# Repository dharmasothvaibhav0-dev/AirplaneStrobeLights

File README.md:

# AirplaneStrobeLights

### This project is designed to replicate the strobe lights seen on flights. The lights flash on the sides of the wings and the top and back of the plane for better visibility.
I got inspiration for this when I went to the airport and saw the planes with these flashing lights, and I wanted to replicate it. 

## Schematic-

## PCB-

## Assembly- 

Its important that you place the LEDS as 2 on the sides, 1 in the middle, and 3 in the back as it is how it is in real life.
I made it so every component can be placed on the top of the PCB, I tried to design it to where it still had a decent look once all components were placed. 

As soon as you connect the plane to a USB A port(5v), it should automatically turn on and the leds will start to flash very quick.

## Components-

This is made up of 10 resistors, **Its very important to know that resistor #1 is 8.2k, and resistor #2 is 1k** All the rest are 220, be very careful. Also **Capacitor 1 is .01u, and Capacitor 2 is 10u**. When placing said resistors and capacitors capacitor 2 goes on the left of the NE555, and Capacitor 1 goes to the right. Resistor 1 goes to the top of capcitor 2, and resistor 2 goes to the top of capacitor 1. its VERY important you place them in the correct spots as seen below.

## Bill of Materials (BOM)

| Id                               | Footprint                                         | Quantity | Value   |
|----------------------------------|---------------------------------------------------|----------|---------|
| C1                               | C_Disc_D8.0mm_W5.0mm_P5.00mm                      | 1        | 0.01uF  |
| C2                               | C_Disc_D8.0mm_W5.0mm_P5.00mm                      | 1        | 10uF    |
| D1, D2, D3, D4, D5, D6, D7, D8   | LED_D5.0mm                                        | 8        | LED     |
| J1                               | USB_A_Molex_67643_Horizontal                      | 1        | USB_A   |
| R1                               | R_Axial_DIN0204_L3.6mm_D1.6mm_P7.62mm_Horizontal  | 1        | 8.2kΩ   |
| R2                               | R_Axial_DIN0204_L3.6mm_D1.6mm_P7.62mm_Horizontal  | 1        | 1kΩ     |
| R4, R5, R6, R7, R8, R9, R10, R11 | R_Axial_DIN0204_L3.6mm_D1.6mm_P7.62mm_Horizontal  | 8        | 220Ω    |
| U1                               | DIP-8_W7.62mm                                     | 1        | NE555P  |
| U2                               | DIP-16_W7.62mm                                    | 1        | CD4017  |

# I hope you enjoy building this! - Vaibhav :D

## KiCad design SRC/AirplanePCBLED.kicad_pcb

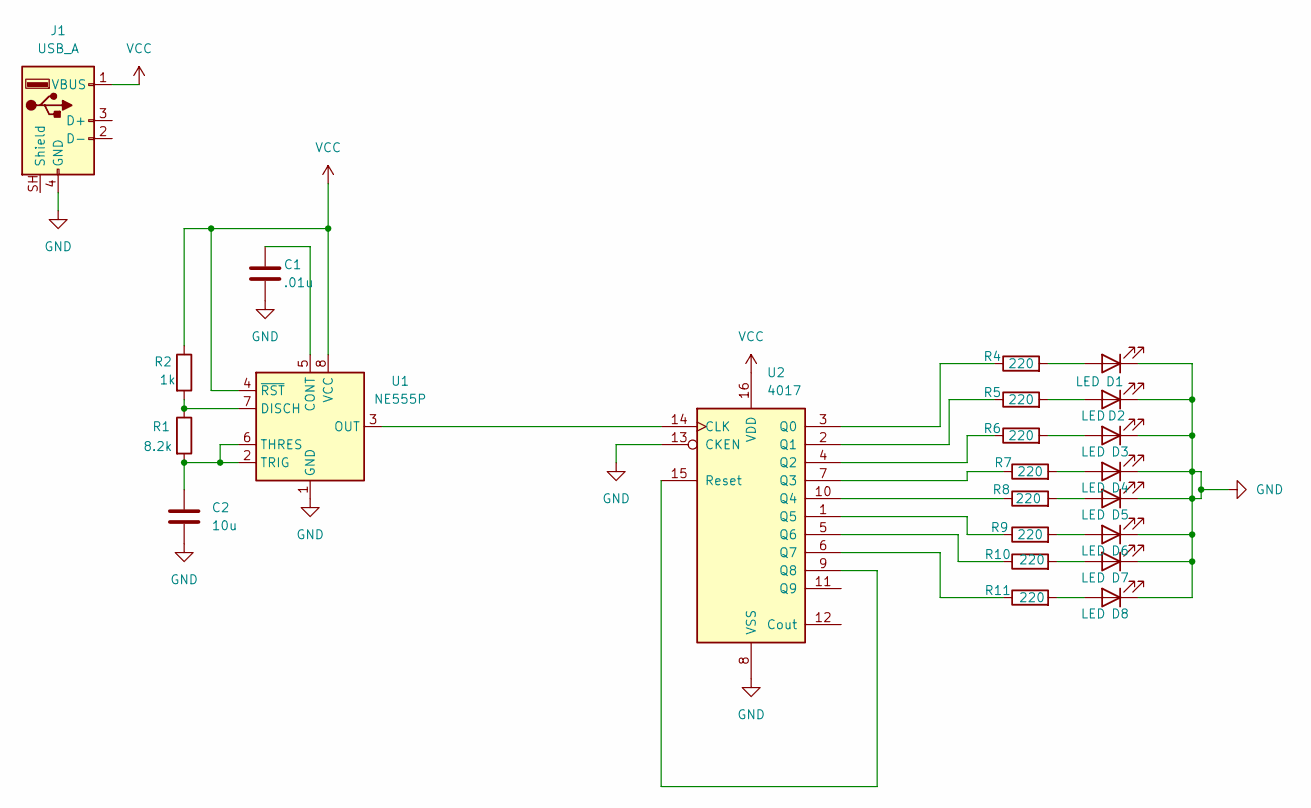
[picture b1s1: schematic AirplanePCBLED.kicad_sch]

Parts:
C1: .01u; C_Disc_D8.0mm_W5.0mm_P5.00mm
C2: 10u; C_Disc_D8.0mm_W5.0mm_P5.00mm
D1, D2, D3, D4, D5, D6, D7, D8: LED; LED_D5.0mm
J1: USB_A; USB_A_Molex_67643_Horizontal
R1: 8.2k; R_Axial_DIN0204_L3.6mm_D1.6mm_P7.62mm_Horizontal
R2: 1k; R_Axial_DIN0204_L3.6mm_D1.6mm_P7.62mm_Horizontal
R4, R5, R6, R7, R8, R9, R10, R11: 220; R_Axial_DIN0204_L3.6mm_D1.6mm_P7.62mm_Horizontal
U1: NE555P; DIP-8_W7.62mm
U2: 4017; DIP-16_W7.62mm

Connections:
GND: C1.2, C2.2, D1.1 (K), D2.1 (K), D3.1 (K), D4.1 (K), D5.1 (K), D6.1 (K), D7.1 (K), D8.1 (K), J1.4 (GND), U1.1 (GND), U2.8 (VSS), U2.13 (CKEN)
unnamed: D1.2 (A), R4.2
unnamed: D2.2 (A), R5.2
unnamed: D3.2 (A), R6.2
unnamed: D4.2 (A), R7.2
unnamed: D5.2 (A), R8.2
unnamed: D6.2 (A), R9.2
unnamed: D7.2 (A), R10.2
unnamed: D8.2 (A), R11.2
unnamed: C1.1, U1.5 (CONT)
unnamed: R1.1, R2.2, U1.7 (DISCH)
unnamed: U1.3 (OUT), U2.14 (CLK)
unnamed: C2.1, R1.2, U1.2 (TRIG), U1.6 (THRES)
unnamed: R4.1, U2.3 (Q0)
unnamed: R5.1, U2.2 (Q1)
unnamed: R6.1, U2.4 (Q2)
unnamed: R7.1, U2.7 (Q3)
unnamed: R8.1, U2.10 (Q4)
unnamed: R9.1, U2.1 (Q5)
unnamed: R10.1, U2.5 (Q6)
unnamed: R11.1, U2.6 (Q7)
unnamed: U2.9 (Q8), U2.15 (Reset)
VCC: J1.1 (VBUS), R2.1, U1.4 (~RST), U1.8 (VCC), U2.16 (VDD)

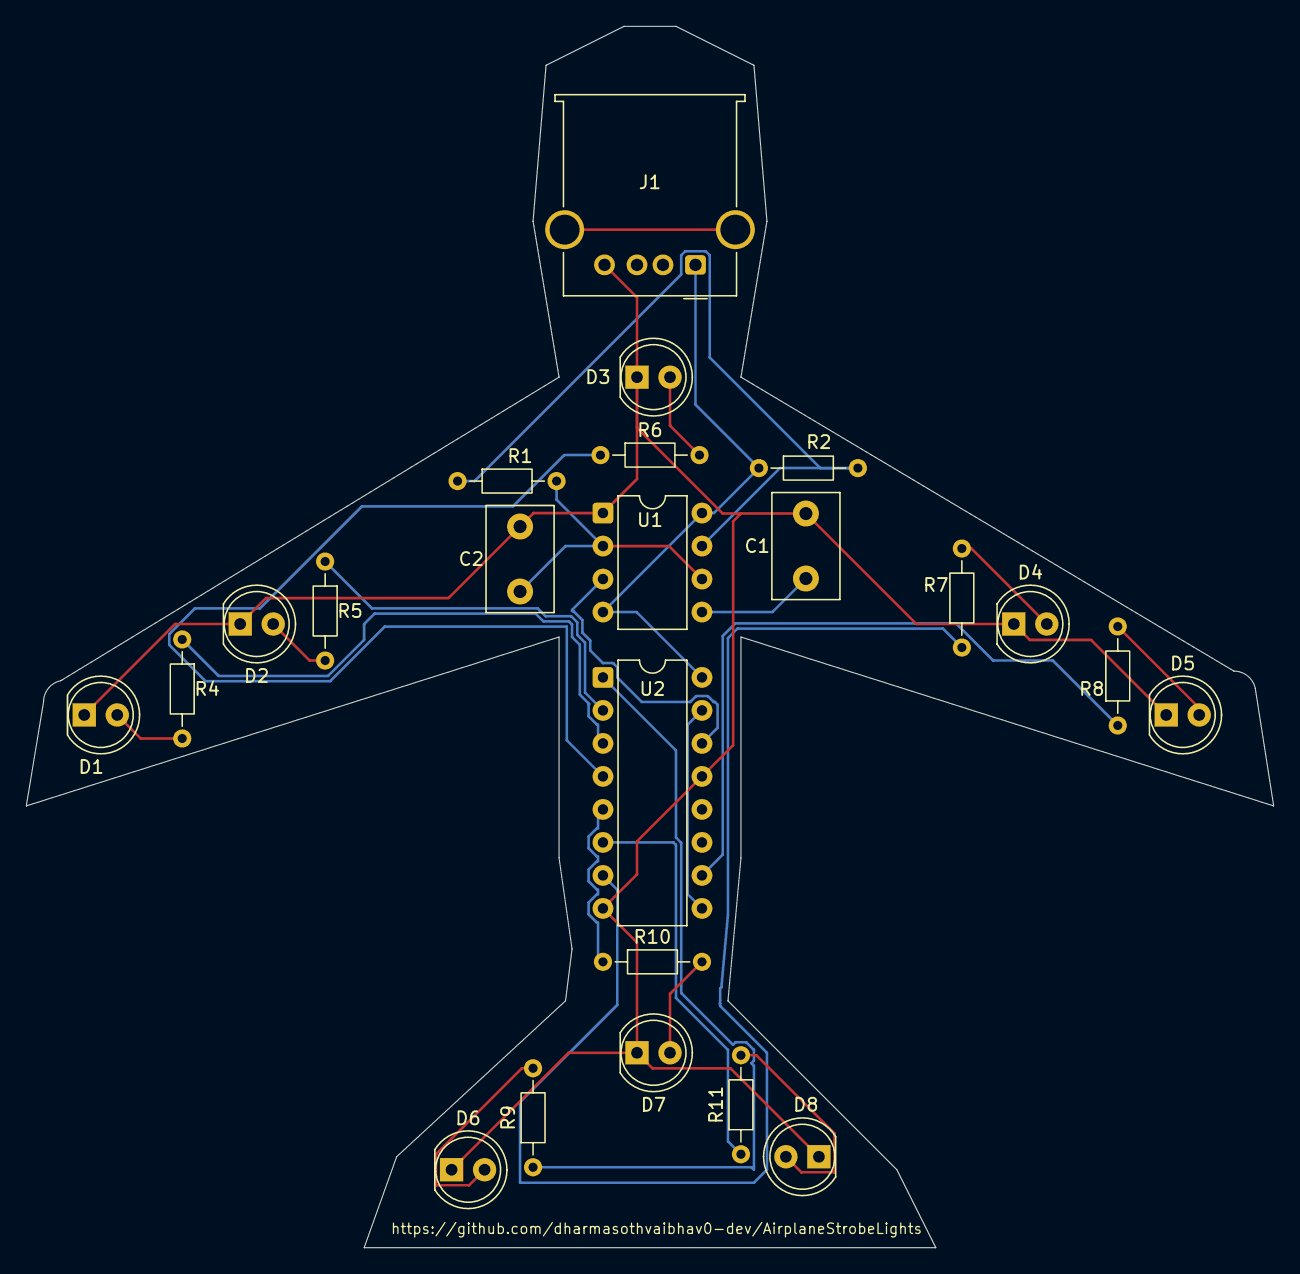
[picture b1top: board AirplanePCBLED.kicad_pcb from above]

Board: 2 copper layers, 96.0 x 94.0 mm, 23 parts (0 on the bottom side), 23 nets.
